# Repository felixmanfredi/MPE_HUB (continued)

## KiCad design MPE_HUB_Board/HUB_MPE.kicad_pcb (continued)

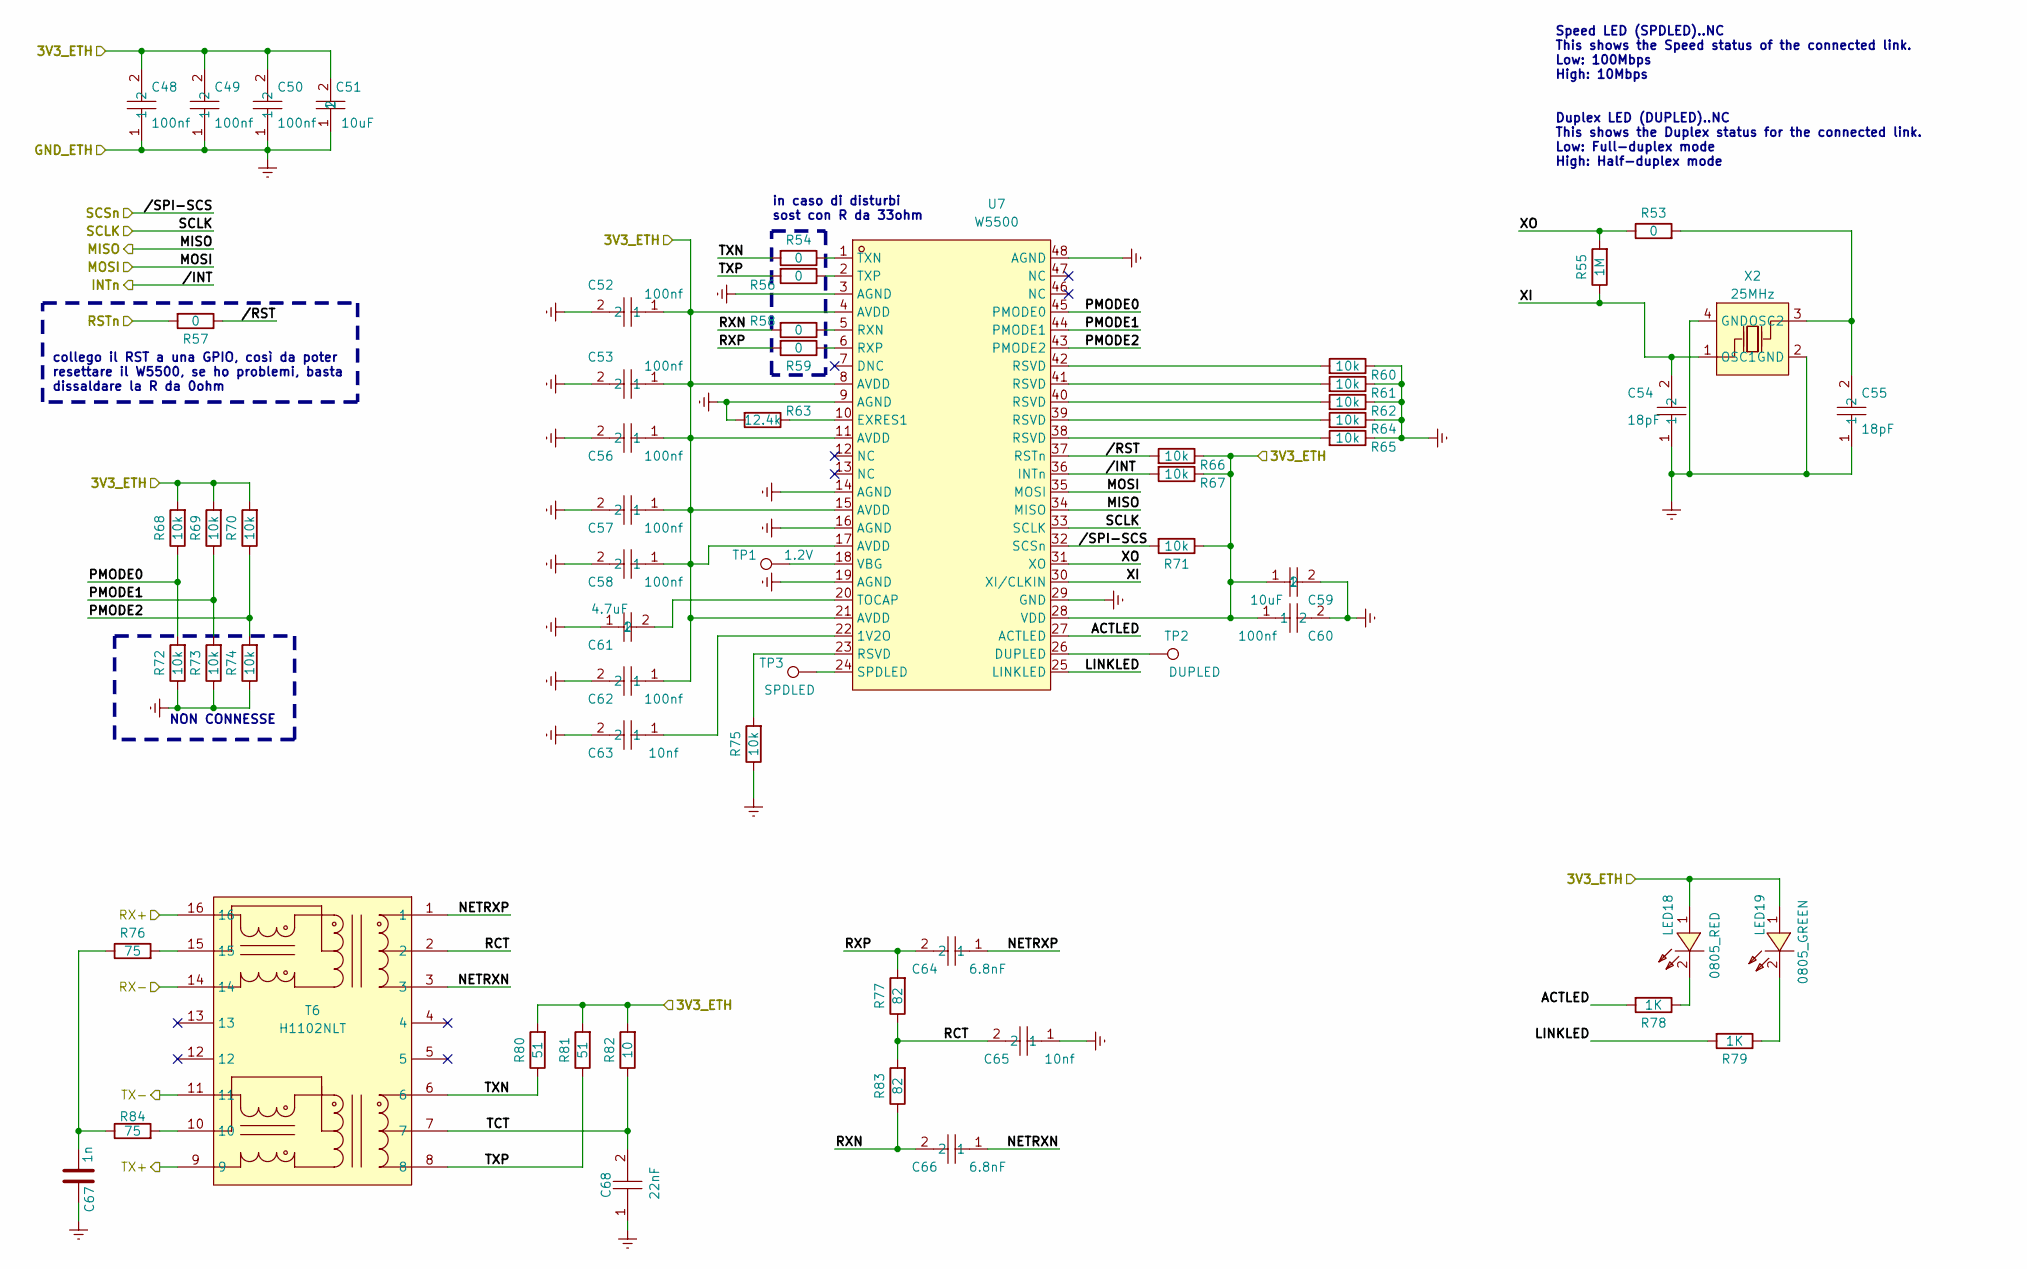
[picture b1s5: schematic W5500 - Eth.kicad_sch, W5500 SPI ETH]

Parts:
C48, C49, C50, C52, C53, C56, C57, C58, C60, C62: 100nf; C_0603_1608Metric; LCSC Part C14663
C51, C59: 10uF; C_0603_1608Metric; LCSC Part C440198
C54, C55: 18pF; C_0603_1608Metric; LCSC Part C165734
C61: 4.7uF; C_0603_1608Metric; LCSC Part C1779
C63, C65: 10nf; C_0603_1608Metric; LCSC Part C57112
C64, C66: 6.8nF; C_0603_1608Metric; LCSC Part C1631
C67: 1n; C_0603_1608Metric; LCSC Part C1588
C68: 22nF; C_0603_1608Metric; LCSC Part C21122
LED18: 0805_RED; LED0805-R-RD; LCSC Part C84256
LED19: 0805_GREEN; LED0805-R-RD; LCSC Part C2297
R53, R54, R56, R57, R58, R59: 0; R_0603_1608Metric; LCSC Part C21189
R55: 1M; R_0603_1608Metric; LCSC Part C105578
R60, R61, R62, R64, R65, R66, R67, R68, R69, R70, R71, R72, R73, R74, R75: 10k; R_0603_1608Metric; LCSC Part C25804
R63: 12.4k; R_0603_1608Metric; LCSC Part C413726
R76, R84: 75; R_0603_1608Metric; LCSC Part C4275
R77, R83: 82; R_0603_1608Metric; LCSC Part C23255
R78, R79: 1K; R_0603_1608Metric; LCSC Part C21190
R80, R81: 51; R_0603_1608Metric; LCSC Part C2074217
R82: 10; R_0603_1608Metric; LCSC Part C510088
T6: H1102NLT; XFMR-SMD_H1102NLT; LCSC Part C18584
TP1: 1.2V; TestPoint_Pad_D1.0mm
TP2: DUPLED; TestPoint_Pad_D1.0mm
TP3: SPDLED; TestPoint_Pad_D1.0mm
U7: W5500; LQFP-48_L7.0-W7.0-P0.50-LS9.0-BL; LCSC Part C32843
X2: 25MHz; CRYSTAL-SMD_4P-L3.2-W2.5-BL; LCSC Part C70593

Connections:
+3.3V: C48.2, C49.2, C50.2, C51.2, C52.1, C53.1, C56.1, C57.1, C58.1, C59.1, C60.1, C62.1, LED18.1 (+), LED19.1 (A), R66.1, R67.1, R68.2, R69.2, R70.2, R71.1, R80.2, R81.2, R82.2, U7.4 (AVDD), U7.8 (AVDD), U7.11 (AVDD), U7.15 (AVDD), U7.17 (AVDD), U7.21 (AVDD), U7.28 (VDD); also elsewhere on the board
/ETH_ESP_RX+: T6.16; also elsewhere on the board
/ETH_ESP_RX-: T6.14; also elsewhere on the board
/ETH_ESP_TX+: T6.9; also elsewhere on the board
/ETH_ESP_TX-: T6.11; also elsewhere on the board
/Ethernet_Module/ACTLED: R78.2, U7.27 (ACTLED)
/Ethernet_Module/LINKLED: R79.2, U7.25 (LINKLED)
/Ethernet_Module/MISO: U7.34 (MISO); also elsewhere on the board
/Ethernet_Module/MOSI: U7.35 (MOSI); also elsewhere on the board
/Ethernet_Module/NETRXN: C66.1, T6.3
/Ethernet_Module/NETRXP: C64.1, T6.1
/Ethernet_Module/PMODE0: R68.1, R72.2, U7.45 (PMODE0)
/Ethernet_Module/PMODE1: R69.1, R73.2, U7.44 (PMODE1)
/Ethernet_Module/PMODE2: R70.1, R74.2, U7.43 (PMODE2)
/Ethernet_Module/RCT: C65.2, R77.1, R83.2, T6.2
/Ethernet_Module/RSTn: R57.2; also elsewhere on the board
/Ethernet_Module/RXN: C66.2, R58.2, R83.1
/Ethernet_Module/RXP: C64.2, R59.2, R77.2
/Ethernet_Module/SCLK: U7.33 (SCLK); also elsewhere on the board
/Ethernet_Module/TCT: C68.2, R82.1, T6.7
/Ethernet_Module/TXN: R54.2, R80.1, T6.6
/Ethernet_Module/TXP: R56.2, R81.1, T6.8
/Ethernet_Module/XI: C54.2, R55.1, U7.30 (XI/CLKIN), X2.1 (OSC1)
/Ethernet_Module/XO: R53.1, R55.2, U7.31 (XO)
/Ethernet_Module//INT: R67.2, U7.36 (INTn); also elsewhere on the board
/Ethernet_Module//RST: R57.1, R66.2, U7.37 (RSTn)
/Ethernet_Module//SPI-SCS: R71.2, U7.32 (SCSn); also elsewhere on the board
unnamed: C67.2, R76.1, R84.1
unnamed: LED18.2 (-), R78.1
unnamed: LED19.2 (K), R79.1
unnamed: R60.2, U7.42 (RSVD)
unnamed: R61.2, U7.41 (RSVD)
unnamed: R62.2, U7.40 (RSVD)
unnamed: R64.2, U7.39 (RSVD)
unnamed: R65.2, U7.38 (RSVD)
unnamed: R75.2, U7.23 (RSVD)
unnamed: R76.2, T6.15
unnamed: R84.2, T6.10
unnamed: C63.1, U7.22 (1V2O)
unnamed: TP2.1, U7.26 (DUPLED)
unnamed: R63.1, U7.10 (EXRES1)
unnamed: R58.1, U7.5 (RXN)
unnamed: R59.1, U7.6 (RXP)
unnamed: TP3.1, U7.24 (SPDLED)
unnamed: C61.2, U7.20 (TOCAP)
unnamed: R54.1, U7.1 (TXN)
unnamed: R56.1, U7.2 (TXP)
unnamed: TP1.1, U7.18 (VBG)
unnamed: C55.2, R53.2, X2.3 (OSC2)

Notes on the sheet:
collego il RST a una GPIO, così da poter resettare il W5500, se ho problemi, basta dissaldare la R da 0ohm
in caso di disturbi sost con R da 33ohm
NON CONNESSE
Speed LED (SPDLED)..NC This shows the Speed status of the connected link. Low: 100Mbps High: 10Mbps Duplex LED (DUPLED)..NC This shows the Duplex status for the connected link. Low: Full-duplex mode High: Half-duplex mode

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
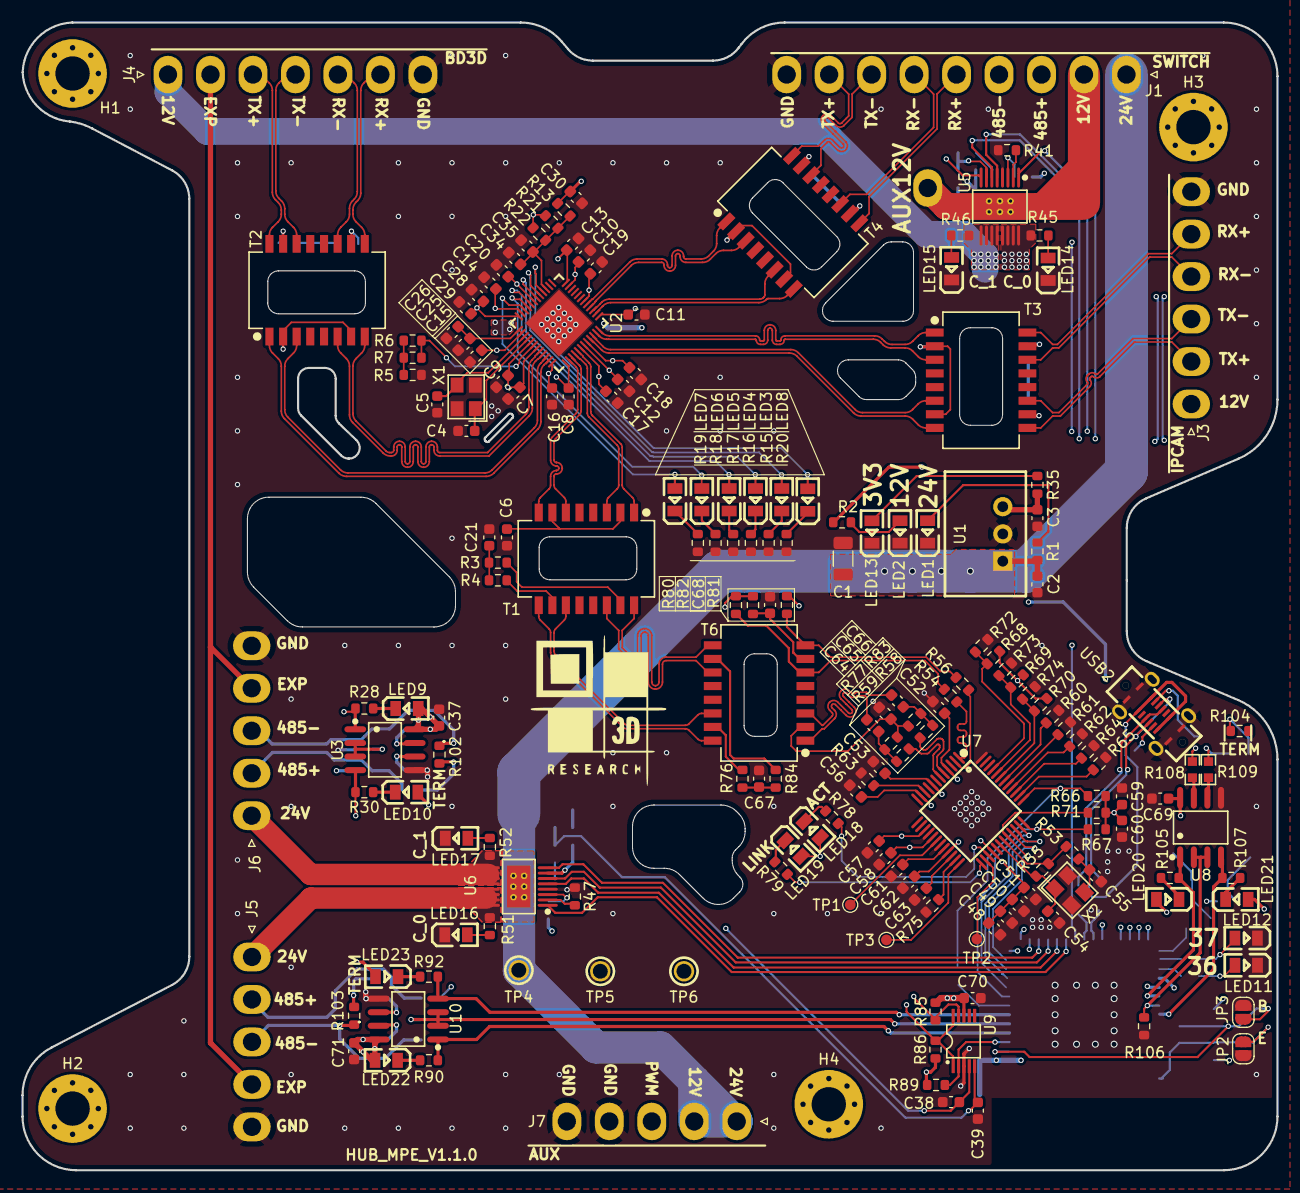
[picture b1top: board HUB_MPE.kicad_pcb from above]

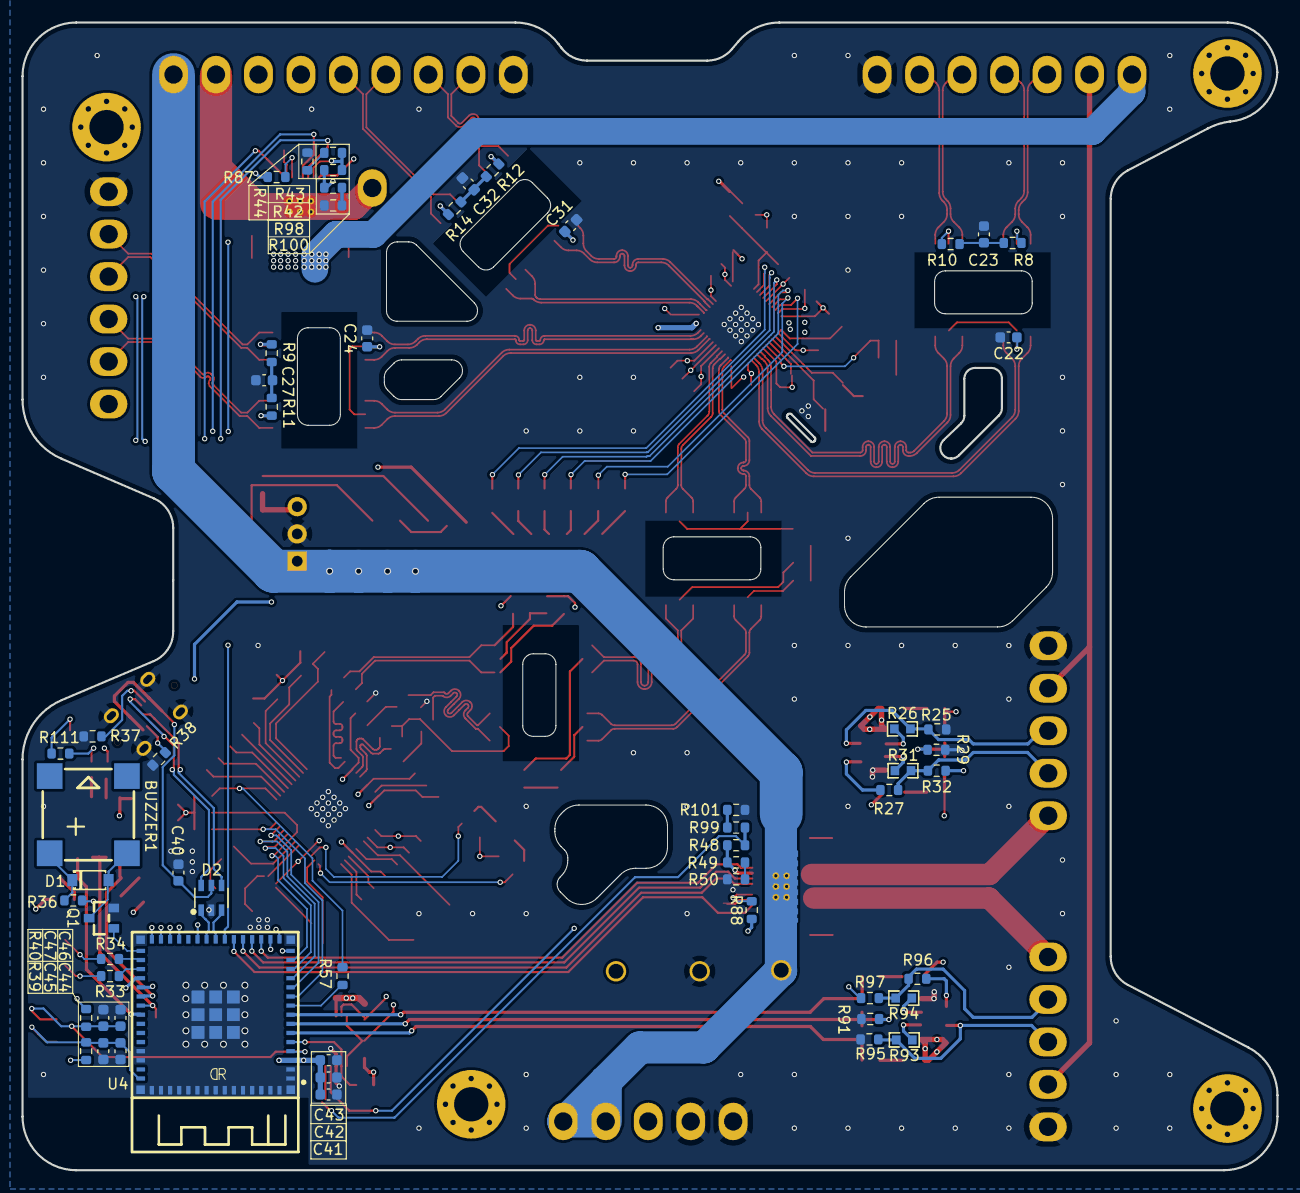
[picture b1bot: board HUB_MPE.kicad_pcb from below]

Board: 4 copper layers, 117.0 x 107.0 mm, 241 parts (58 on the bottom side), 197 nets.

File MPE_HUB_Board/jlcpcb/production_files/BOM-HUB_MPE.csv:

Comment,Designator,Footprint,LCSC,Quantity
1M,R55,R_0603_1608Metric,C105578,1
22uF,C43,C_0603_1608Metric,C12891,1
100n,"C10,C11,C12,C13,C14,C15,C16,C17,C18,C19,C20,C22,C24,C25,C26,C28,C29,C30,C31,C35,C37,C38,C39,C40,C42,C44,C46,C48,C49,C50,C52,C53,C56,C57,C58,C6,C60,C62,C7,C8,C9",C_0603_1608Metric,C14663,41
1u,"C34,C45,C47",C_0603_1608Metric,C15849,3
1n,"C21,C23,C27,C32,C67",C_0603_1608Metric,C1588,5
6.8nF,"C64,C66",C_0603_1608Metric,C1631,2
20pF,"C4,C5",C_0603_1608Metric,C1648,2
18pF,"C54,C55",C_0603_1608Metric,C165734,2
4.7uF,C61,C_0603_1608Metric,C1779,1
H1102NLT,"T1,T2,T3,T4,T6",XFMR-SMD_H1102NLT,C18584,5
10uF 35V,C2,C_0603_1608Metric,C194427,1
51,"R80,R81",R_0603_1608Metric,C2074217,2
AO3400A,"Q10,Q11,Q2,Q3,Q4,Q5,Q6,Q7,Q8,Q9",SOT-23-3_L2.9-W1.3-P1.90-LS2.4-BR,C20917,10
1N4148W T4,D1,SOD-123_L2.8-W1.8-LS3.7-RD,C2099,1
22nF,C68,C_0603_1608Metric,C21122,1
0,"R13,R26,R31,R36,R44,R5,R50,R53,R54,R56,R57,R58,R59",R_0603_1608Metric,C21189,13
1K,"R15,R16,R17,R18,R19,R20,R78,R79",R_0603_1608Metric,C21190,8
120,R27,R_0603_1608Metric,C22787,1
15k,"R101,R103,R41,R42,R47,R48,R85,R87,R89,R91,R93,R95,R97,R99",R_0603_1608Metric,C22809,14
220,"R30,R34,R35",R_0603_1608Metric,C22962,3
0805_GREEN,"LED10,LED12,LED13,LED19,LED3,LED4,LED5,LED6,LED7",LED0805-R-RD,C2297,9
2k,"R1,R2,R45,R46,R51,R52",R_0603_1608Metric,C22975,6
300,"R28,R33",R_0603_1608Metric,C23025,2
4.99K,"R6,R7",R_0603_1608Metric,C23046,2
330,"R43,R49",R_0603_1608Metric,C23138,2
82,"R77,R83",R_0603_1608Metric,C23255,2
100k,R29,R_0603_1608Metric,C25803,1
10k,"R100,R102,R104,R39,R40,R60,R61,R62,R64,R65,R66,R67,R68,R69,R70,R71,R72,R73,R74,R75,R86,R88,R90,R92,R94,R96,R98",R_0603_1608Metric,C25804,27
200k,"R21,R22",R_0603_1608Metric,C25811,2
USBLC6-2SC6_C2687116,D2,SOT-23-6_L2.9-W1.6-P0.95-LS2.8-BL,C2687116,1
33uF 35V,C1,CAP-SMD_BD6.3-L6.6-W6.6-FD,C27784,1
K7803M-1000R3_C2916516,U1,PWRM-TH_DEXU_K78XXM-1000R3_XXXXXX,C2916516,1
RTL8305NB-VB-CG,U2,QFN-48_L6.0-W6.0-P0.40-TL-EP4.4,C3010343,1
ESP32-S3-MINI-1-N4R2,U4,BULETM-SMD_ESP32-S3-MINI-1-N8,C3013941,1
W5500,U7,LQFP-48_L7.0-W7.0-P0.50-LS9.0-BL,C32843,1
12.4k,R63,R_0603_1608Metric,C413726,1
75,"R10,R11,R12,R14,R3,R4,R76,R8,R84,R9",R_0603_1608Metric,C4275,10
10uF,"C51,C59",C_0603_1608Metric,C440198,2
VND7050AJTR,"U5,U6",POWERSSO-16_L4.9-W3.9-P0.50-LS6.0-BL-EP,C443997,2
10,R82,R_0603_1608Metric,C510088,1
IRLML0100TRPBF,Q1,SOT-23_L2.9-W1.3-P1.90-LS2.4-BR,C53658,1
10nf,"C41,C63,C65",C_0603_1608Metric,C57112,3
22uF 10V,C3,C_0603_1608Metric,C60077,1
MAX3485ESA,U3,SOP-8_L5.0-W4.0-P1.27-LS6.0-BL,C668204,1
25MHz,X2,CRYSTAL-SMD_4P-L3.2-W2.5-BL,C70593,1
0805_RED,"LED1,LED11,LED14,LED15,LED16,LED17,LED18,LED2,LED8,LED9",LED0805-R-RD,C84256,10
25Mhz,X1,CRYSTAL-SMD_4P-L3.2-W2.5-BL,C9006,1
MLT-8530,BUZZER1,BUZ-SMD_4P-L8.5-W8.5-P8.50-BR,C94599,1
1.2V,TP1,TestPoint_Pad_D3.0mm,,1
SPDLED,TP3,TestPoint_Pad_D3.0mm,,1
DUPLED,TP2,TestPoint_Pad_D3.0mm,,1

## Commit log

2025-04-03 PCB + PCBA
    Schematic, PCB, BOM, Gerber
2025-04-07 Riadattamento dimensioni scheda
    Offset verso l'interno di 1 mm per ingombri meccanici
2025-04-24 Primo Firmware MPE_HUB
2025-05-02 Aggiornamento 02/05/2025
2025-05-06 Aggiornamento 06/05/2025
2025-05-08 Implementazione 485 e modifiche per test a banco
2025-05-16 Aggiunta setup per angular
2025-05-22 update 22/05/2025
    implementazione OTA
2025-05-26 Implementazione server e richieste POST/GET
2025-05-28 Versione WiFi completa
2025-05-30 (In fase di sviluppo) implementazione ethernet SPI
2025-06-03 Versione con Ethernet funzionante
2025-06-04 Versione WiFi + Ethernet (04/06/2025)
2025-06-05 Ethernet + WiFi + 485 funzionante
2025-06-06 update 06-06-2025 IP-Statico
2025-06-11 update 11/06/2025
2025-06-18 update 18/16/2025
2025-06-18 Versione firmware provvisoria da testare 18/06/2025
2025-06-20 Risolto problema reset (Nel firmware V2)
2025-06-24 Update 24/06/2025
    Aggiunta interfaccia web (da terminare)
2025-06-26 Add new feature to user dashboard
2025-07-03 update 03/07/2025
2025-07-04 Update 04/07/2025
2025-07-08 Update 08/07/2025
2025-07-11 HUB Hardware V1.1.0
2025-07-18 Update 18/07/2025
2025-07-28 update 28/07/2025
2025-08-08 Update 08/08/2025
2025-09-05 Prima versione stabile HUB_V1.1
2025-09-24 update 24/09/2025
2025-10-10 update 10/10/2025
2025-10-21 Stable firmware version 1.3.2
    Introduced a new 'flash' function and button in the UI for lamp control. Updated firmware logic to track torch mode status and improved lamp ID validation. Refactored web server endpoints for lamp co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
2025-11-11 V1.3.4 bug fix
2025-11-27 Update 27/11/2025
